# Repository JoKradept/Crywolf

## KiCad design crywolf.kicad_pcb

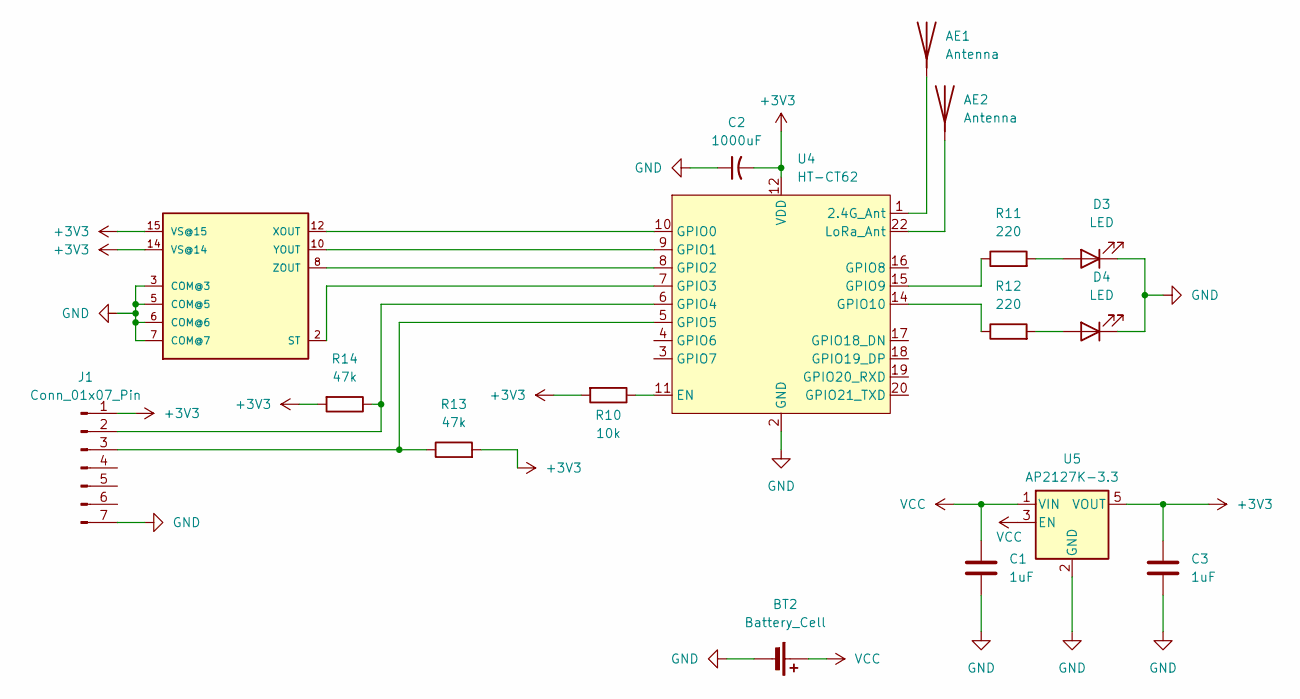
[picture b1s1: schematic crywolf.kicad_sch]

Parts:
AE1, AE2: Antenna; U.FL_Molex_MCRF_73412-0110_Vertical
BT2: Battery_Cell; JST_PH_S2B-PH-K_1x02_P2.00mm_Horizontal
C1, C3: 1uF; C_0603_1608Metric
C2: 1000uF; CP_EIA-7343-31_Kemet-D
D3, D4: LED; LED_0603_1608Metric
J1: Conn_01x07_Pin; PinHeader_1x07_P2.54mm_Vertical
R10: 10k; R_0603_1608Metric
R11, R12: 220; R_0603_1608Metric
R13, R14: 47k; R_0603_1608Metric
U4: HT-CT62; Heltec_HT-CT62
U5: AP2127K-3.3; SOT-23-5
U7: ADXL335; LFCSP-16-4X4

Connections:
+3V3: C2.2, C3.1, J1.1, R10.2, R13.2, R14.2, U4.12 (VDD), U5.5 (VOUT), U7.14 (VS@14), U7.15 (VS@15)
GND: BT2.2 (-), C1.2, C2.1, C3.2, D3.1 (K), D4.1 (K), J1.7, U4.2 (GND), U4.13 (GND), U4.21 (GND), U5.2 (GND), U7.3 (COM@3), U7.5 (COM@5), U7.6 (COM@6), U7.7 (COM@7)
unnamed: AE1.1 (A_1), U4.1 (2.4G_Ant)
unnamed: AE2.1 (A_1), U4.22 (LoRa_Ant)
unnamed: D3.2 (A), R11.2
unnamed: D4.2 (A), R12.2
unnamed: J1.2, R14.1, U4.6 (GPIO4)
unnamed: J1.3, R13.1, U4.5 (GPIO5)
unnamed: R10.1, U4.11 (EN)
unnamed: U4.10 (GPIO0), U7.12 (XOUT)
unnamed: U4.9 (GPIO1), U7.10 (YOUT)
unnamed: U4.8 (GPIO2), U7.8 (ZOUT)
unnamed: U4.7 (GPIO3), U7.2 (ST)
unnamed: R11.1, U4.15 (GPIO9)
unnamed: R12.1, U4.14 (GPIO10)
VCC: BT2.1 (+), C1.1, U5.1 (VIN), U5.3 (EN)

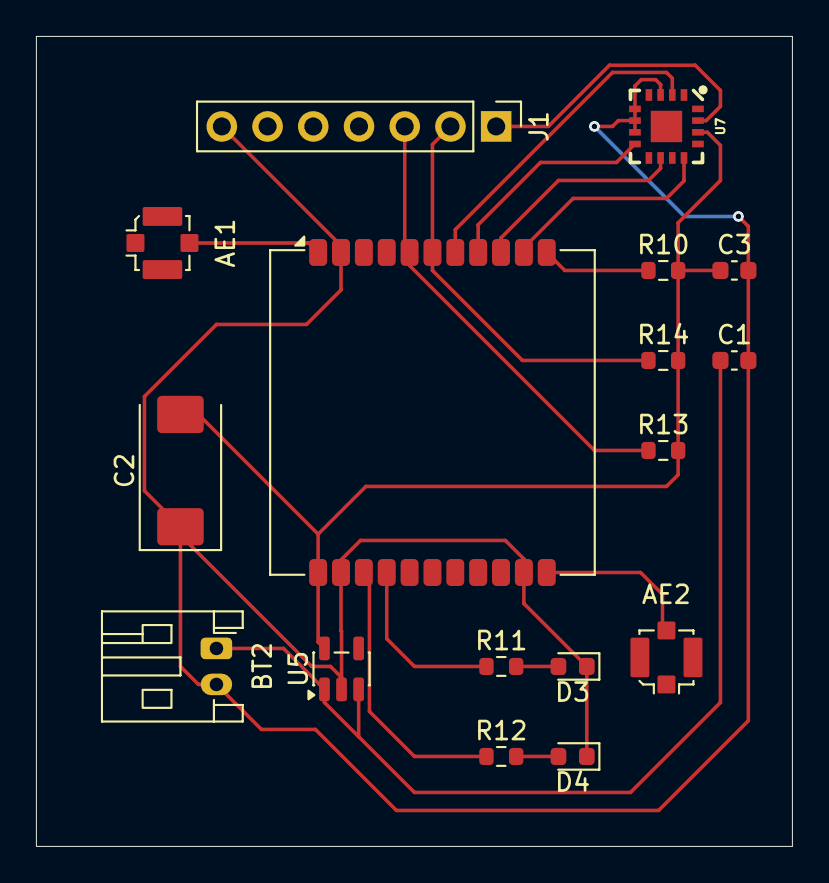
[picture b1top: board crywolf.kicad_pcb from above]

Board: 2 copper layers, 42.0 x 45.0 mm, 17 parts (0 on the bottom side), 16 nets.

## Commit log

2026-04-20 Create a
